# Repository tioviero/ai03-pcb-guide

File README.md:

# ai03-pcb-guide
 Very first keyboard PCB designed through the use of ai03's guide @ https://wiki.ai03.com/books/pcb-design/chapter/pcb-designer-guide

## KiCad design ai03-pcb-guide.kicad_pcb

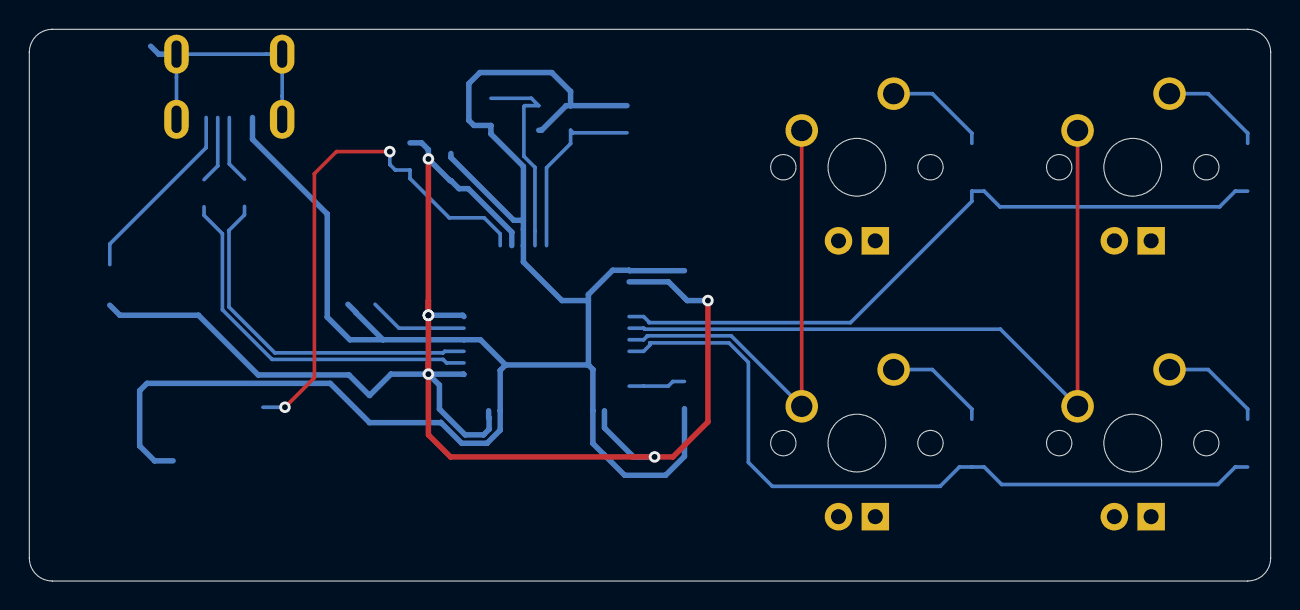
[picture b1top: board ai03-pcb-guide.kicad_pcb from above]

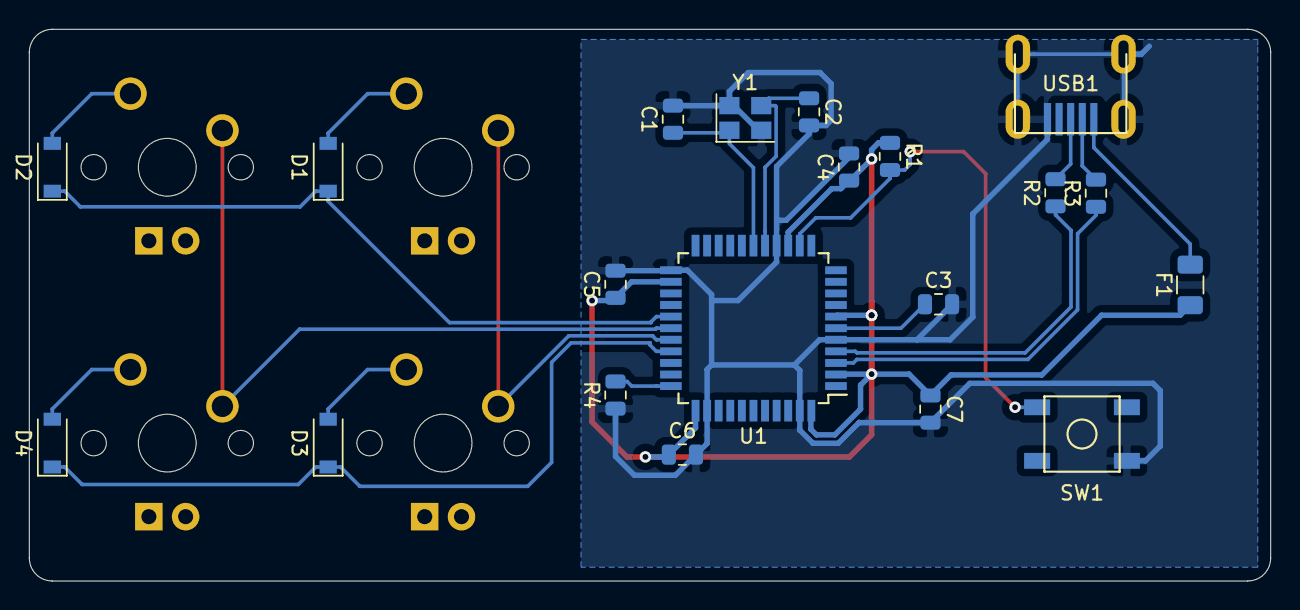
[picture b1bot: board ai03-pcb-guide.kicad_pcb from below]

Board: 2 copper layers, 85.7 x 38.1 mm, 24 parts (20 on the bottom side), 20 nets.

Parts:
C1, C2: 22pF; C_0805_2012Metric
C3: 1uF; C_0805_2012Metric
C4, C5, C6: 0.1uF; C_0805_2012Metric
C7: 10uF; C_0805_2012Metric
D1, D2, D3, D4: SOD-123; D_SOD-123
F1: 500mA; Fuse_1206_3216Metric
MX1, MX2, MX3, MX4: MX-NoLED; MXOnly-1U
R1, R4: 10k; R_0805_2012Metric
R2, R3: 22; R_0805_2012Metric
SW1: SW_Push; SKQG-1155865
U1: ATmega32U4-AU; TQFP-44_10x10mm_P0.8mm
USB1: Molex-0548190589
Y1: 16MHz; Crystal_SMD_3225-4Pin_3.2x2.5mm

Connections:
+5V: C4.1, C5.1, C6.1, C7.1, F1.1, R1.1, U1.2, U1.7, U1.14, U1.24, U1.34, U1.44
COL0: MX1.1, MX3.1, U1.29
COL1: MX2.1, MX4.1, U1.28
D+: R2.2, USB1.3
D-: R3.2, USB1.4
GND: C1.2, C2.2, C3.2, C4.2, C5.2, C6.2, C7.2, R4.1, SW1.1, U1.5, U1.15, U1.23, U1.35, U1.43, USB1.1, USB1.6, Y1.2, Y1.4
unnamed: C1.1, U1.17, Y1.1
unnamed: C2.1, U1.16, Y1.3
unnamed: C3.1, U1.6
unnamed: D1.2, MX1.2
unnamed: D2.2, MX2.2
unnamed: D3.2, MX3.2
unnamed: D4.2, MX4.2
unnamed: R1.2, SW1.2, U1.13
unnamed: R2.1, U1.4
unnamed: R3.1, U1.3
unnamed: R4.2, U1.33
ROW0: D1.1, D2.1, U1.27
ROW1: D3.1, D4.1, U1.30
VCC: F1.2, USB1.5

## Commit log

2024-07-17 Initialize project
2024-07-17 Add submodules
2024-07-17 Add footprint libraries
2024-07-17 uC and USB Mini-B Schematic
2024-07-17 Add updated MX submodule
2024-07-18 Completed schematic
2024-07-18 Partial PCB Progress
2024-07-18 PCB Progress
2024-07-18 Finalized PCB Design
2024-07-18 Completed PCB
